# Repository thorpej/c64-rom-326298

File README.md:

# ROM replacer module for Commodore 64s

This is a module that replaces the 3 mask ROMs in a Commodore 64 with a
single parallel NOR flash ROM chip that's extremely reliable and still,
as of October 2023, being manufactured.  Why would you want to do this?
Well, sometimes these old MOS mask ROMs fail, and when they do, you have
to replace them with a newer part.  And to do *that*, you will probably
have to use some sort of adapter to fit a newer EPROM or EEPROM chip into
the socket.  Well, if you're going install an adapter anyway, why not just
do it once?

In addition to improved reliability, this module draws less power and
produces less heat than the original mask ROMs.  Furthermore, because
the flash ROM is a larger capacity (128KB) and reprogrammable, it can
also hold 3 alternate ROM images for each ROM in addition to the
standard ROM image (for a total of 4 each).  3 sets of DIP switches are
provided to select between the ROM images.

While originally designed for my 326298 Rev A board, this will work
in the other Commodore 64 longboards that have 3 24-pin ROM sockets.

This work is licensed under the [Creative Commons Attribution
ShareAlike 4.0 International license](https://creativecommons.org/licenses/by-sa/4.0/).

## How it works

The theory of operation of the module is quite simple.  Each of the
3 mask ROMs are connected to the system address bus (A0-A12 for the
BASIC and KERNAL ROMs, A0-A11 for the Character ROM), the system data
bus, and their own individual chip select, which are controlled by
the PLA.  The module intercepts all of these signals at the ROM sockets.

The 128KB flash ROM is divided into 3 segments:

* A 32KB segment to hold up to 4 8KB KERNAL ROM images.
* A 32KB segment to hold up to 4 8KB BASIC ROM images.
* A 16KB segment to hold up to 4 4KB Character ROM images.

These segments are selected by decoding the mask ROM chip selects and
mapping them to the A15-A16 address inputs to the flash ROM:

* 00 - KERNAL
* 01 - BASIC
* 10 - Character
* 11 - (not used)

Within each segment, 2 DIP switches control the upper 2 bits of the
offset within the segment:

* A13-A14 for the KERNAL and BASIC segments.
* A12-A13 for the Character segment (A14 is always 0 in this case).

Because A12's behavior is dependent on which ROM segment is selected,
the decoding logic intercepts it and adjusts it as necessary.

The decoding, segment selection, and image selection logic is implemented
in a GAL22V10.  The logic equations can be found in
[gal-files/c64-128k-rom-mux.gal](gal-files/c64-128k-rom-mux.gal).  You can
read the comments in that file for a more detailed explanation of what's
going on, but here are the basic rules:

* The flash ROM CE# and OE# signals are asserted when exactly one of the
  3 mask ROM chip selects are asserted.
* Because the value of the A12 input to the flash ROM is dependent on
  which mask ROM is being selected, the assertion of CE# and OE# is delayed
  by one propagation delay through the GAL, ensuring that A12 will be stable
  before the output is enabled.
* The individual image selection within the selected segment follows the DIP
  switch setting corresponding to which of the 3 mask ROMs is being selected.

The module has pins that make the following connections to the mask ROM
sockets on the C64 board:

* U3 - 1-24 (all pins)
* U4 - 20, 21
* U5 - 9-24

## How to build it

Building the module is pretty simple.  I've used all through-hole parts
to make it easier to assemble for the casual hobbyist.  You only need a
few parts.  Most of the parts can be purchased from [Jameco Electronics](https://www.jameco.com),
a small business located in the San Francisco Bay Area that's been serving
the elctronics hobbyist community for decades.  Alas, there are a few items
on the list that Jameco doesn't have, so I've provided links to the parts on
Mouser, as well, at least for one parts that Mouser carries (alas, Mouser
does not carry all of these parts, either).

* One of the **c64-rom-326298** PCBs.  The Gerber files are provided
here and I have set up a shared project on PCBWay [here](https://www.pcbway.com/project/shareproject/ROM_Replacer_board_for_Commodore_64W55451ASS34_c64_rom_326298_1_0_gerbers_e5988f98.html).
* A standard DIP-32 0.6 inch socket for the flash chip.  I prefer the
machined type (Jameco part number [**105381**](https://www.jameco.com/z/ICM-632-1-GT-James-Electronics-32-Pin-Machine-Tooled-Low-Profile-IC-Socket-0-6-Inch-Wide_105381.html)).
* A standard DIP-24 0.3 inch socket for the GAL22V10.  Again, I prefer
the machined type (Jameco part number [**39386**](https://www.jameco.com/z/24MTLP-3-Jameco-ValuePro-Socket-IC-24-Pin-Machine-Tooled-Slimline-Low-Profile-Soldertail-3-Width_39386.html)).
* *Only if your ROM are not already in sockets*, 3 standard DIP-24 0.6 inch
sockets to receive the ROM replacer board.  For these, the dual-leaf type
sockets are actually better because they're a little more tolerant of pins
that are not perfectly-aligned (Jameco part number [**112264**](https://www.jameco.com/z/6000-24W-James-Electronics-24-Pin-Dual-Wipe-Low-Profile-IC-Socket-0-6-Inch-Wide_112264.html)).
* 2 100nF / 0.1uF ceramic capacitors with 2.54mm lead spacing that
fits into a 4mm x 2.6mm footprint (Jameco part number [**25523**](https://www.jameco.com/z/MD-1-James-Electronics-Monolithic-Ceramic-Capacitor-0-1-micro-F-50V-20-_25523.html) or Mouser part number [**594-K104K15X7RF5UL2**](https://www.mouser.com/ProductDetail/Vishay-BC-Components/K104K15X7RF5UL2?qs=rLgk8CAOBHbCqsnkGO2HJA%3D%3D) are good candidates).
* 1 7-pin 4.7K ohm bussed 6-resistor array in a SIP package (Jameco part number [**24660**](https://www.jameco.com/z/10BRN4-7K-4310R-101-472--James-Electronics-10-Pin-125-mWatt-4-7k-Ohm-2-Bussed-Resistor-Network_24660.html) or Mouser part
numbers [**279-SIL07E472J**](https://www.mouser.com/ProductDetail/TE-Connectivity-AMP/SIL07E472J?qs=8G8kQhBkhGgEfy%2FI59SPVQ%3D%3D) or [**652-4607X-1LF-4.7K**](https://www.mouser.com/ProductDetail/Bourns/4607X-101-472LF?qs=s5SGu2UNbPR%252Bh5Zd6JQ4tg%3D%3D)).
* A Microchip **SST39SF010A** 128k x 8 flash ROM chip, DIP-32 package
(Mouser part number [**804-39SF010A7CPHE**](https://www.mouser.com/ProductDetail/Microchip-Technology/SST39SF010A-70-4C-PHE?qs=QvO7Tx5jqMVuuIOitIyveA%3D%3D)).
* A Lattice **GAL22V10** (-15 or -25) or Atmel / Microchip **ATF22V10C-15PU**.  Lattice GAL22V10s can be acquired on the secondary electronics market (eBay, AliExpress, etc.).  ATF22V10Cs can be acquired
from the usual electronics suppliers (Mouser part number
[**556-AF22V10C15PU**](https://www.mouser.com/ProductDetail/Microchip-Technology/ATF22V10C-15PU?qs=2mdvTlUeTfCr46ZvfjTtAg%3D%3D)).
* 3 2-position SPST DIP switches (Jameco part number [**109059**](https://www.jameco.com/z/KAS1102E-JVP-Jameco-ValuePro-2-Position-Raised-Slide-DIP-Switch-On-Off-SPST-PC-Pins-2-54mm-Through-Hole_109059.html) or Mouser part number [**653-A6E2104N**](https://www.mouser.com/ProductDetail/Omron-Electronics/A6E-2104-N?qs=vyIerDHf%2Fml%252BIzczbpFO%252Bw%3D%3D)).
* Round (machine tooled) pin headers to populate 42 pins.  I usually buy
these on AliExpress in bulk and have them on-hand,
[here](https://www.aliexpress.us/item/3256801585843343.html), for example.
I have been told that these pin headers can be found on Mouser with Mouser
part number [**200-MTSW15007TS180**](https://www.mouser.com/ProductDetail/Samtec/MTSW-150-07-T-S-180?qs=Cqqh%252BS766wn5xlRZ3985zg%3D%3D), although I have not
verified this myself!  Anyway, you must use this type because the usual square
pin headers will damage the sockets on the C64 main board.

You must use sockets for the ICs for two reasons:
* There must be clearance for the pins that face downward towards the
C64 main board, some of which are below the ICs on the board.
* You probably want to be able to remove the flash chip at some point to
reprogram it with additional ROM images.

(I suppose you *could* solder the GAL to the board after programming it
if you really wanted to, but really it's best practice to put it in a socket,
in my opinion.)

You will also need a programmer to program the GAL and the flash ROM chip.
I use a TL866II Plus, which can program both the Lattice and Atmel / Microchip
versions of the 22V10.  You want to program the 22V10 with the file
[gal-files/c64-128k-rom-mux.jed](gal-files/c64-128k-rom-mux.jed).  I do not
supply ROM images for the flash chip.  You'll need to provide those yourself,
either by dumping your existing ROMs or by getting ROM images another way
(e.g. from [zimmers.net](http://www.zimmers.net/anonftp/pub/cbm/firmware/computers/c64/index.html)).

If the mask ROMs are not socketed in your Commodore 64, then you need
to de-solder the orignal ROMs and install the DIP-24 sockets mentioned
in the parts list above.  Do this first!

When assembling the board, you want to get the downward-facing pin headers
that insert into the ROM sockets as vertically aligned as possible.  One
way to doing this is to insert the pins into a breadboard, set the board
down on top of the pins, and hold the board flat as you tack a couple of
the pins to the board to keep it still while you finish the rest.  Other
option is to insert the header into the board, tack one pin to the board
and then, while heating that one solder joint, carefully moving the header
around until it is perfectly perpindicular.  Just be careful not to burn
your fingers!

Next, place the chip sockets on the PCB, flip the PCB over, and solder
the sockets to the PCB from the bottom side.

Next, populate the ceramic capacitors and resistor array and solder
them into place.

Finally, populate the 3 2-position DIP switches with the "ON" position
being towards the flash ROM socket and solder them into place.

I've provided a small command line tool, [mkflashimg.sh](mkflashimg.sh), to
make it easy to assemble a flash ROM image.  It's a shell script that should
run just fine on Linux, NetBSD/FreeBSD, macOS, and maybe even Cygwin.  Here
is an example of how to run the tool:

    dhcp-194:thorpej$ ./mkflashimg.sh -k kernal.901227-02.bin -k kernal.901227-03.bin -k JiffyDOS_C64_6.01.bin -k JiffyDOS_C64_6.01.bin -b basic.901226-01.bin -c characters.901225-01.bin c64-rom-326298.bin
    $KERNAL_0='kernal.901227-02.bin'
    $KERNAL_1='kernal.901227-03.bin'
    $KERNAL_2='JiffyDOS_C64_6.01.bin'
    $KERNAL_3='JiffyDOS_C64_6.01.bin'
    $BASIC_0='basic.901226-01.bin'
    $BASIC_1='empty'
    $BASIC_2='empty'
    $BASIC_3='empty'
    $Character_0='characters.901225-01.bin'
    $Character_1='empty'
    $Character_2='empty'
    $Character_3='empty'

    Write flash image to 'c64-rom-326298.bin' (y/n)? y

    -rw-r--r--  1 thorpej  staff  81920 Dec 14 16:13 c64-rom-326298.bin
    dhcp-194:thorpej$

In this example, I've put the original rev 2 KERNAL for my machine in KERNAL
slot 0, the rev 3 KERNAL in KERNAL slot 1, and JiffyDOS in slots 2 and 3 (so
that no matter the setting of the "0" bit of the KERNAL selector switch, if
the "1" bit is set, I will always get JiffyDOS).  Once you've assembled
the flash ROM image, use the programmer of your choice to write it to the
flash ROM chip.

And that's it!  Just pop the programmed flash chip and GAL into the sockets,
set the DIP switches to select the ROM images of your choice, insert the
module into the C64, and enjoy!

There are other ways you can use this board, too!  For example, if you
buy a JiffyDOS ROM chip, a switch is provided to let you select JiffyDOS
or the stock KERNAL.  If you want to install such a switch, all you need
to do is tack the wires from the switch to the appropriate DIP switch solder
pads on the board; if either the DIP switch or external switch for that
position is set to "on", then that switch position will be "on".  It's up to
you to decide if you want to drill a hole in your precious Commodore 64 to do
this!

If you have any questions about the board, you can reach out to me on
Twitter (*[@thorpej](https://twitter.com/thorpej)*) or Mastodon
(*[@thorpej@mastodon.sdf.org](https://mastodon.sdf.org/@thorpej)*).  You
can also check out my [YouTube channel](https://www.youtube.com/@thorpejsf),
which has this and other retrocomputing related content.

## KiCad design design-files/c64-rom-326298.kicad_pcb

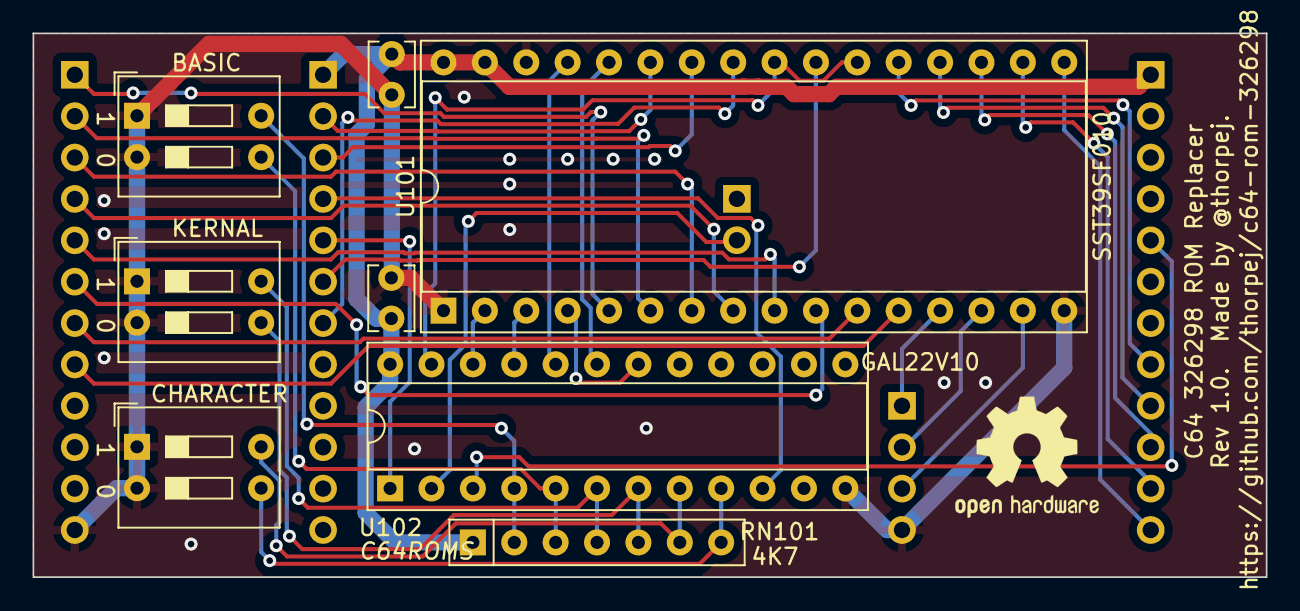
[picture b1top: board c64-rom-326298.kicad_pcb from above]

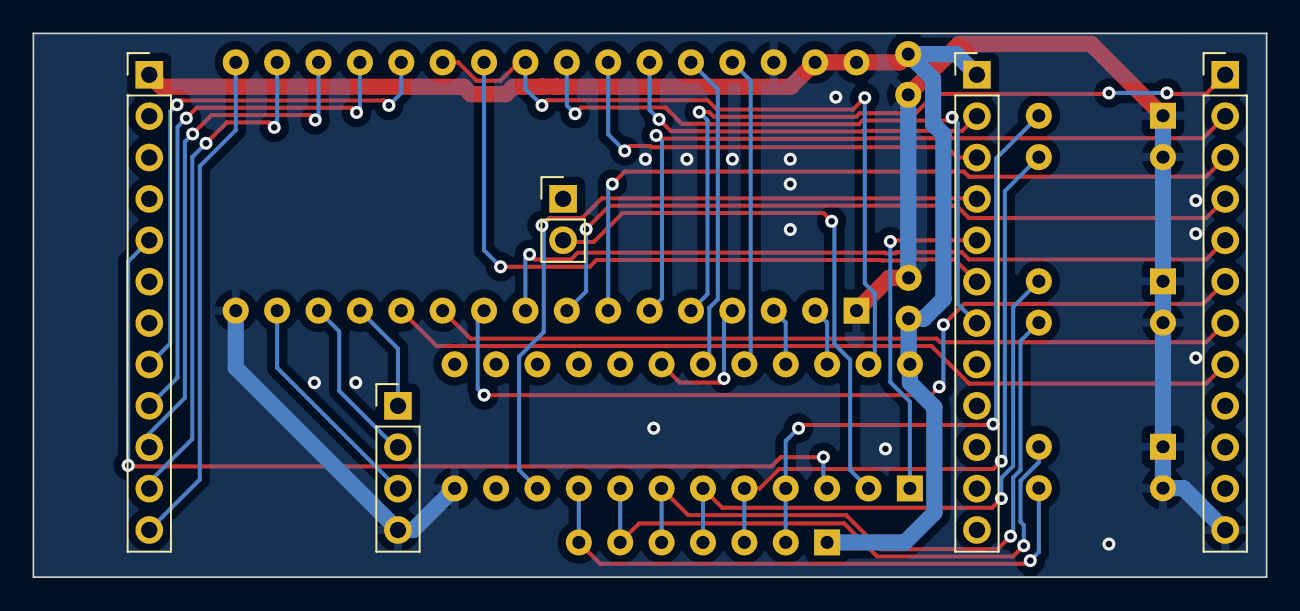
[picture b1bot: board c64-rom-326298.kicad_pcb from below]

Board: 2 copper layers, 75.7 x 33.4 mm, 13 parts (5 on the bottom side), 38 nets.

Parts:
C101, C102: 0.1µF; C_Disc_D3.8mm_W2.6mm_P2.50mm
J1, J2, J5: Conn_01x12_Pin; PinHeader_1x12_P2.54mm_Vertical
J3: Conn_01x02_Pin; PinHeader_1x02_P2.54mm_Vertical
J4: Conn_01x04_Pin; PinHeader_1x04_P2.54mm_Vertical
RN101: 4K7; R_Array_SIP7
SW101, SW102, SW103: SW_DIP_x02; SW_DIP_SPSTx02_Slide_9.78x7.26mm_W7.62mm_P2.54mm
U101: SST39SF010; DIP-32_W15.24mm_Socket
U102: GAL22V10; DIP-24_W7.62mm_Socket

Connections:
A0: J1.8, U101.12 (A0)
A1: J1.7, U101.11 (A1)
A2: J1.6, U101.10 (A2)
A3: J1.5, U101.9 (A3)
A4: J1.4, U101.8 (A4)
A5: J1.3, U101.7 (A5)
A6: J1.2, U101.6 (A6)
A7: J1.1, U101.5 (A7)
A8: J2.2, U101.27 (A8)
A9: J2.3, U101.26 (A9)
A10: J2.6, U101.23 (A10)
A11: J2.7, U101.25 (A11)
D0: J4.1, U101.13 (D0)
D1: J4.2, U101.14 (D1)
D2: J4.3, U101.15 (D2)
D3: J5.12, U101.17 (D3)
D4: J5.11, U101.18 (D4)
D5: J5.10, U101.19 (D5)
D6: J5.9, U101.20 (D6)
D7: J5.8, U101.21 (D7)
IA12: J2.4, U102.10 (I10)
unnamed: RN101.2 (R1), SW101.4, U102.4 (I4)
unnamed: RN101.3 (R2), SW101.3, U102.5 (I5)
unnamed: RN101.4 (R3), SW102.4, U102.6 (I6)
unnamed: RN101.5 (R4), SW102.3, U102.7 (I7)
unnamed: RN101.6 (R5), SW103.4, U102.8 (I8)
unnamed: RN101.7 (R6), SW103.3, U102.9 (I9)
unnamed: U101.4 (A12), U102.18 (IO5)
unnamed: U101.28 (A13), U102.19 (IO6)
unnamed: U101.29 (A14), U102.20 (IO7)
unnamed: U101.3 (A15), U102.21 (IO8)
unnamed: U101.2 (A16), U102.22 (IO9)
unnamed: U101.22 (CE), U101.24 (OE), U102.23 (IO10)
VCC: C101.1, C102.1, J2.1, J5.1, RN101.1 (common), U101.31 (PGM), U101.32 (VCC), U102.24 (VCC)
VSS: C101.2, C102.2, J1.12, J4.4, SW101.1, SW101.2, SW102.1, SW102.2, SW103.1, SW103.2, U101.1 (NC), U101.16 (GND), U101.30 (NC), U102.12 (GND)
~BAS: J2.5, U102.1 (I1/CLK)
~CHR: J5.5, U102.3 (I3)
~KRN: J3.2, U102.2 (I2)

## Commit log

2023-10-31 ROM replacer / selector board for the C64 326298.
2023-10-31 Fix name / company on schematic sheet.
2023-10-31 Add URL to the board.
2023-10-31 More ground plane action.
2023-11-01 The readme!
2023-11-01 Add Jameco part number for the DIP switches, correct # of pins that need to be populated.
2023-11-01 Add LICENSE file.
2023-11-01 memory -> ROM
2023-11-01 Fix a drag glitch in the schematic.
2023-11-01 Don't forget the resistor array!
2023-12-13 Re-arrange the inputs to the GAL and make them active-low.
2023-12-13 Correct ROM socket pin header spacing.
2023-12-14 Fix some wording, add reference to license.
2023-12-14 Re-route the boards after fixing the pin spacing.
2023-12-14 Plot the Gerbers for rev 1.0.
2023-12-14 Add images of the board and a PDF copy of the schematic.
2023-12-14 Fix typo.
2023-12-15 Add a tool to generate the flash ROM images.
2024-01-26 Update the README with additional part information and instructions.
2024-02-11 Successfully tested in all C64 longboard revisions.

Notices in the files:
README.md:
CC BY-SA 4.0
design-files/c64-rom-326298.kicad_pcb:
Copyright (c) 2023 Jason R. Thorpe. See LICENSE.
